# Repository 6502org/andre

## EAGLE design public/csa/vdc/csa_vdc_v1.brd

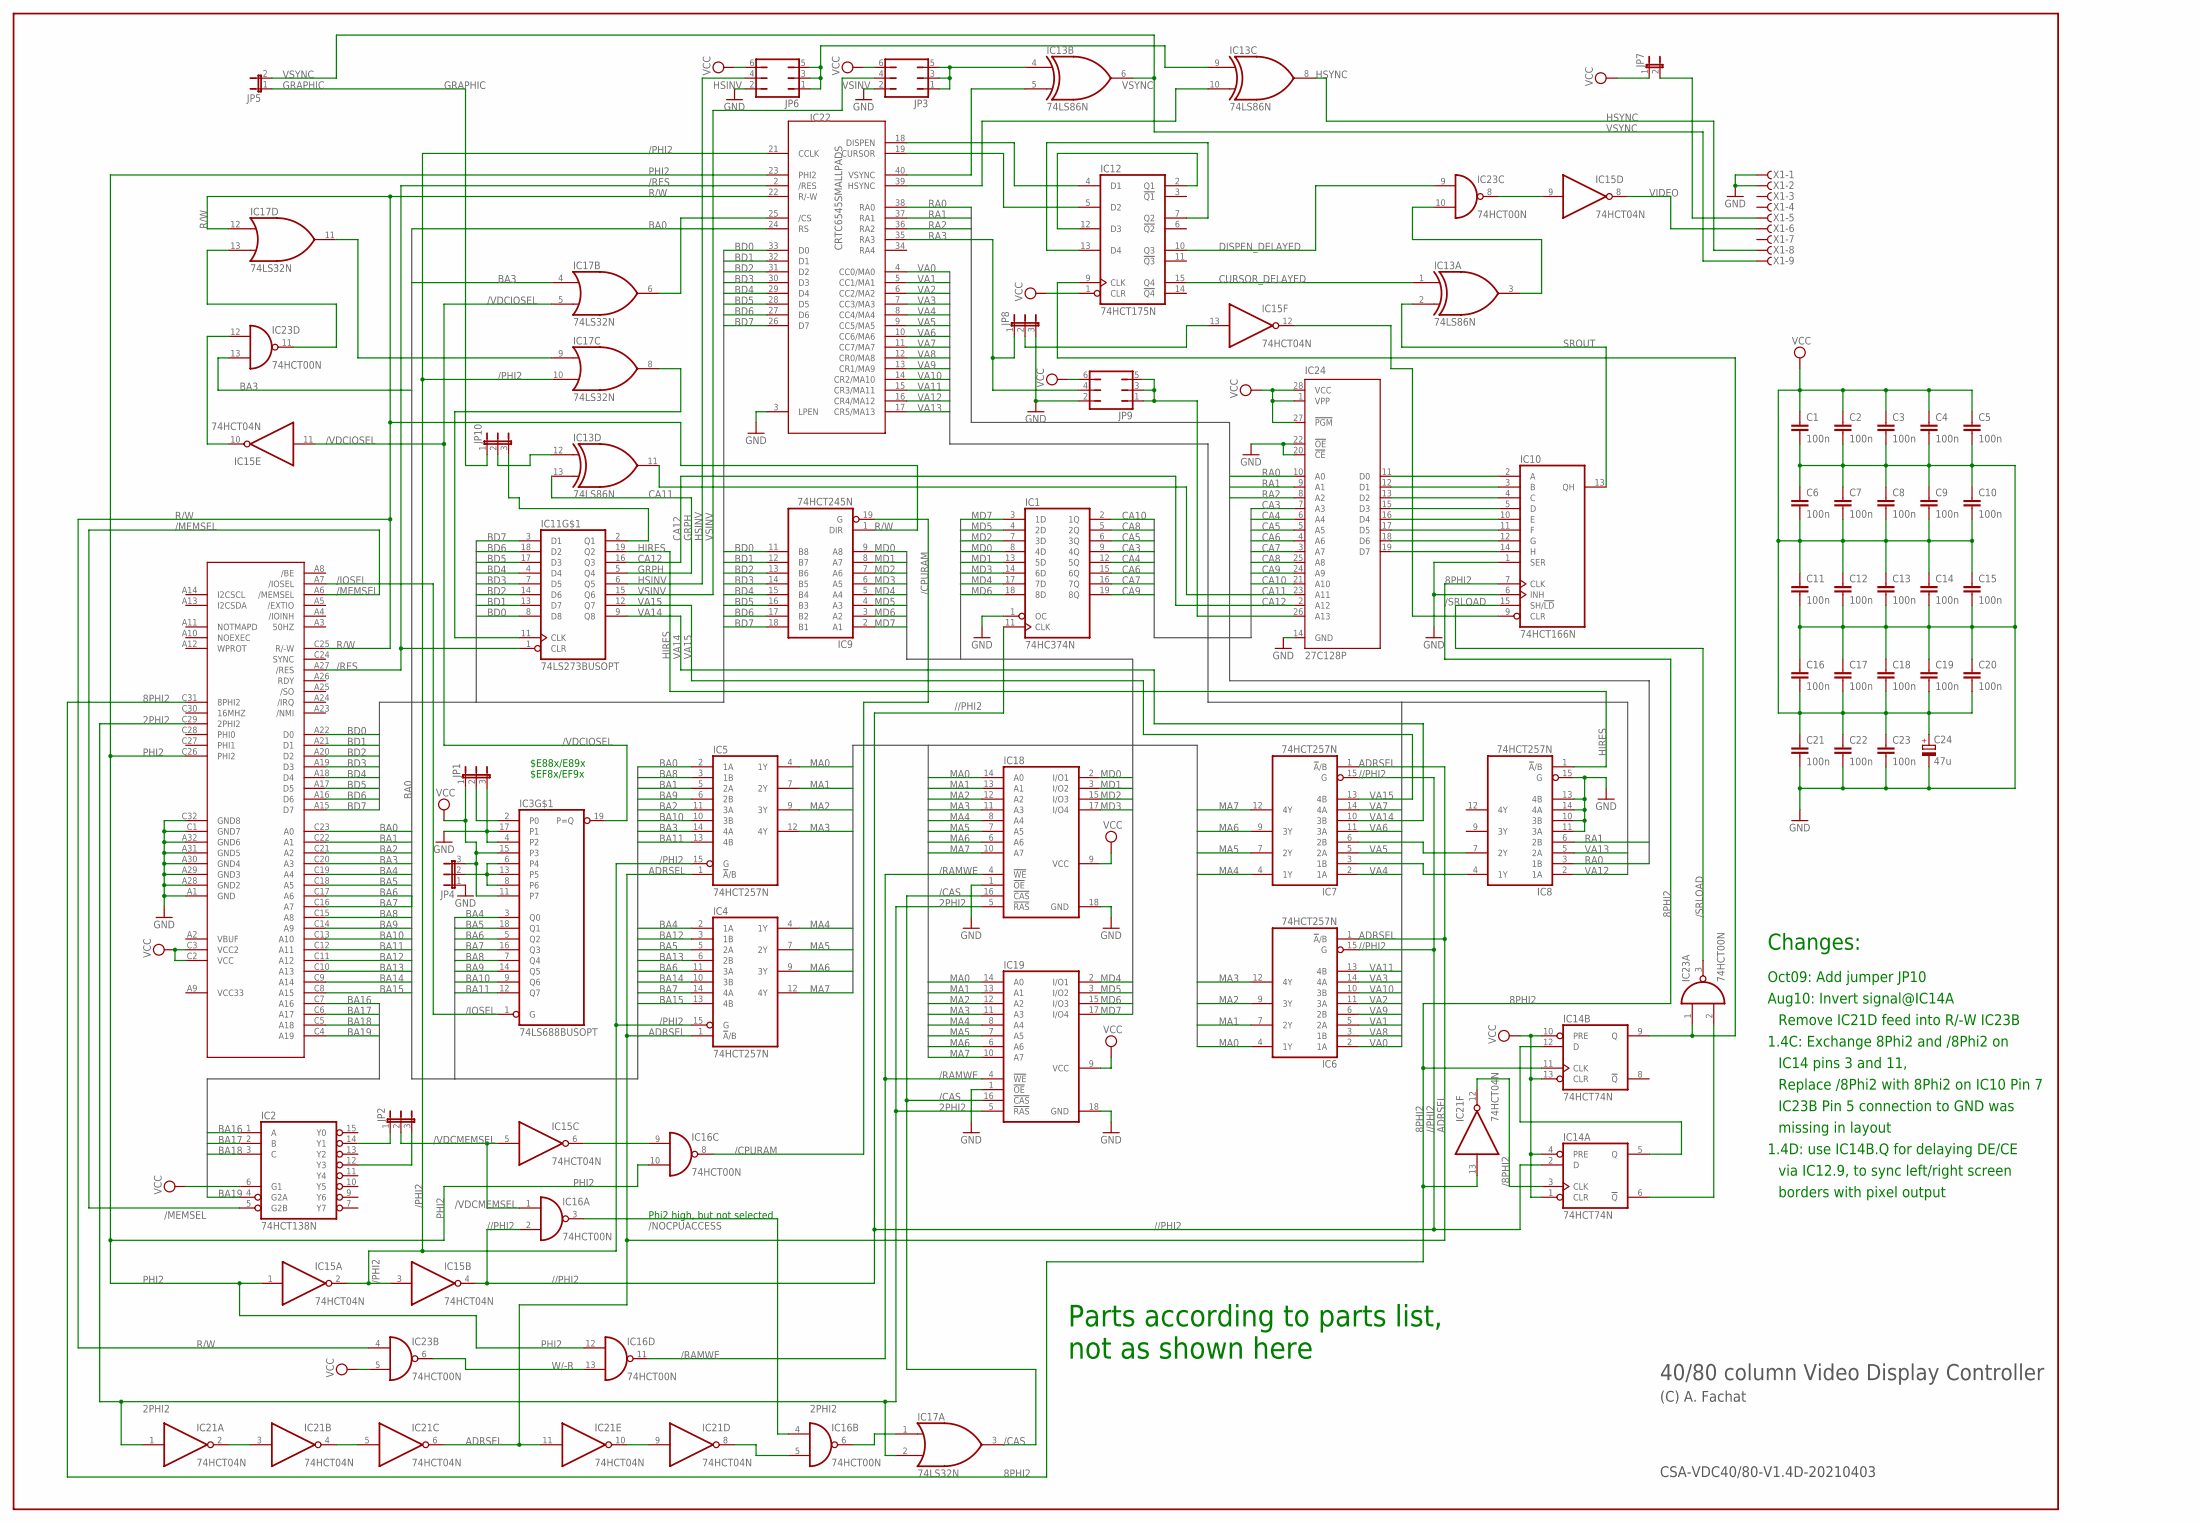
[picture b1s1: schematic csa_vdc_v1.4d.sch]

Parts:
C1, C2, C3, C4, C5, C6, C7, C8, C9, C10, C11, C12, C13, C14, C15, C16, C17, C18, C19, C20, C21, C22, C23: 100n; C025-025X050
C24: 47u; E2,5-5
IC1: 74HC374N; DIL20
IC2: 74HCT138N; DIL16
IC3: 74LS688BUSOPT; DIL20
IC4, IC5, IC6, IC7, IC8: 74HCT257N; DIL16
IC9: 74HCT245N; DIL20
IC10: 74HCT166N; DIL16
IC11: 74LS273BUSOPT; DIL20
IC12: 74HCT175N; DIL16
IC13: 74LS86N; DIL14
IC14: 74HCT74N; DIL14
IC15, IC21: 74HCT04N; DIL14
IC16, IC23: 74HCT00N; DIL14
IC17: 74LS32N; DIL14
IC18, IC19: 41464C; DIL18
IC22: CRTC6545SMALLPADS; DIP40
IC24: 27C128P; DIL28-6
JP1, JP2, JP4, JP8, JP10: JP2E; JP2
JP3, JP6, JP9: JP3Q
JP5, JP7: JP1E; JP1
U$1: CSABUS
X1: F09HPS; F09HP

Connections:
2PHI2: IC17.2 (I1), IC18.5 (!RAS), IC19.5 (!RAS), IC21.1 (I), U$1.C29 (2PHI2)
8PHI2: IC10.7 (CLK), IC14.11 (CLK), IC21.13 (I), U$1.C31 (8PHI2)
/8PHI2: IC14.3 (CLK), IC21.12 (O)
//PHI2: IC1.11 (CLK), IC6.15 (G), IC7.15 (G), IC14.2 (D), IC15.4 (O), IC16.2 (I1)
/CAS: IC17.3 (O), IC18.16 (!CAS), IC19.16 (!CAS)
/CPURAM: IC9.19 (G), IC16.8 (O)
/IOSEL: IC3.1 (G), U$1.A7 (/IOSEL)
/MEMSEL: IC2.5 (G2B), U$1.A6 (/MEMSEL)
/NOCPUACCESS: IC16.3 (O), IC16.4 (I0)
/PHI2: IC4.15 (G), IC5.15 (G), IC15.2 (O), IC15.3 (I), IC17.10 (I1), IC22.21 (CCLK)
/RAMWE: IC16.11 (O), IC18.4 (!WE), IC19.4 (!WE)
/RES: IC11.1 (CLR), IC22.2 (/RES), U$1.A27 (/RES)
/SRLOAD: IC10.15 (SH/!LD), IC23.3 (O)
/VDCIOSEL: IC3.19 (P=Q), IC15.11 (I), IC17.5 (I1)
/VDCMEMSEL: IC15.5 (I), IC16.1 (I0), JP2.2
ADRSEL: IC4.1 (!A!/B), IC5.1 (!A!/B), IC6.1 (!A!/B), IC7.1 (!A!/B), IC21.6 (O), IC21.11 (I)
BA0: IC5.2 (1A), IC22.24 (RS), U$1.C23 (A0)
BA1: IC5.5 (2A), U$1.C22 (A1)
BA2: IC5.11 (3A), U$1.C21 (A2)
BA3: IC5.14 (4A), IC17.4 (I0), IC23.13 (I1), U$1.C20 (A3)
BA4: IC3.3 (Q0), IC4.2 (1A), U$1.C19 (A4)
BA5: IC3.18 (Q1), IC4.5 (2A), U$1.C18 (A5)
BA6: IC3.5 (Q2), IC4.11 (3A), U$1.C17 (A6)
BA7: IC3.16 (Q3), IC4.14 (4A), U$1.C16 (A7)
BA8: IC3.7 (Q4), IC5.3 (1B), U$1.C15 (A8)
BA9: IC3.14 (Q5), IC5.6 (2B), U$1.C14 (A9)
BA10: IC3.9 (Q6), IC5.10 (3B), U$1.C13 (A10)
BA11: IC3.12 (Q7), IC5.13 (4B), U$1.C12 (A11)
BA12: IC4.3 (1B), U$1.C11 (A12)
BA13: IC4.6 (2B), U$1.C10 (A13)
BA14: IC4.10 (3B), U$1.C9 (A14)
BA15: IC4.13 (4B), U$1.C8 (A15)
BA16: IC2.1 (A), U$1.C7 (A16)
BA17: IC2.2 (B), U$1.C6 (A17)
BA18: IC2.3 (C), U$1.C5 (A18)
BA19: IC2.4 (G2A), U$1.C4 (A19)
BD0: IC9.11 (B8), IC11.8 (D8), IC22.33 (D0), U$1.A22 (D0)
BD1: IC9.12 (B7), IC11.13 (D7), IC22.32 (D1), U$1.A21 (D1)
BD2: IC9.13 (B6), IC11.14 (D6), IC22.31 (D2), U$1.A20 (D2)
BD3: IC9.14 (B5), IC11.7 (D5), IC22.30 (D3), U$1.A19 (D3)
BD4: IC9.15 (B4), IC11.4 (D4), IC22.29 (D4), U$1.A18 (D4)
BD5: IC9.16 (B3), IC11.17 (D3), IC22.28 (D5), U$1.A17 (D5)
BD6: IC9.17 (B2), IC11.18 (D2), IC22.27 (D6), U$1.A16 (D6)
BD7: IC9.18 (B1), IC11.3 (D1), IC22.26 (D7), U$1.A15 (D7)
CA3: IC1.9 (4Q), IC24.7 (A3)
CA4: IC1.12 (5Q), IC24.6 (A4)
CA5: IC1.6 (3Q), IC24.5 (A5)
CA6: IC1.15 (6Q), IC24.4 (A6)
CA7: IC1.16 (7Q), IC24.3 (A7)
CA8: IC1.5 (2Q), IC24.25 (A8)
CA9: IC1.19 (8Q), IC24.24 (A9)
CA10: IC1.2 (1Q), IC24.21 (A10)
CA11: IC13.11 (O), IC24.23 (A11)
CA12: IC11.16 (Q3), IC24.2 (A12)
CURSOR_DELAYED: IC12.15 (Q4), IC13.1 (I0)
DISPEN_DELAYED: IC12.10 (Q3), IC23.9 (I0)
GND: C1.2, C2.2, C3.2, C4.2, C5.2, C6.1, C7.1, C8.1, C9.1, C10.1, C11.2, C12.2, C13.2, C14.2, C15.2, C16.1, C17.1, C18.1, C19.1, C20.1, C21.2, C22.2, C23.2, C24.-, IC1.1 (OC), IC1.10 (GND), IC2.8 (GND), IC3.4 (P2), IC3.10 (GND), IC3.17 (P1), IC4.8 (GND), IC5.8 (GND), IC6.8 (GND), IC7.8 (GND), IC8.8 (GND), IC8.10 (3B), IC8.11 (3A), IC8.13 (4B), IC8.14 (4A), IC8.15 (G), IC9.10 (GND), IC10.1 (SER), IC10.6 (INH), IC10.8 (GND), IC11.10 (GND), IC12.8 (GND), IC13.7 (GND), IC14.7 (GND), IC15.7 (GND), IC16.7 (GND), IC17.7 (GND), IC18.1 (!OE), IC18.18 (GND), IC19.1 (!OE), IC19.18 (GND), IC21.7 (GND), IC22.1 (GND), IC22.3 (LPEN), IC23.7 (GND), IC24.14 (GND), IC24.20 (!CE), IC24.22 (!OE), JP1.3, JP3.2, JP4.1, JP6.2, JP8.3, JP9.2, U$1.A1 (GND), U$1.A28 (GND2), U$1.A29 (GND3), U$1.A30 (GND4), U$1.A31 (GND5), U$1.A32 (GND6), U$1.C1 (GND7), U$1.C32 (GND8), X1.1, X1.2
GRAPHIC: JP5.1, JP10.1
GRPH: IC11.5 (Q4), IC13.13 (I1)
HIRES: IC8.1 (!A!/B), IC11.19 (Q2)
HSINV: IC11.6 (Q5), JP6.4
HSYNC: IC13.8 (O), X1.8
MA0: IC5.4 (1Y), IC6.4 (1Y), IC18.14 (A0), IC19.14 (A0)
MA1: IC5.7 (2Y), IC6.7 (2Y), IC18.13 (A1), IC19.13 (A1)
MA2: IC5.9 (3Y), IC6.9 (3Y), IC18.12 (A2), IC19.12 (A2)
MA3: IC5.12 (4Y), IC6.12 (4Y), IC18.11 (A3), IC19.11 (A3)
MA4: IC4.4 (1Y), IC7.4 (1Y), IC18.8 (A4), IC19.8 (A4)
MA5: IC4.7 (2Y), IC7.7 (2Y), IC18.7 (A5), IC19.7 (A5)
MA6: IC4.9 (3Y), IC7.9 (3Y), IC18.6 (A6), IC19.6 (A6)
MA7: IC4.12 (4Y), IC7.12 (4Y), IC18.10 (A7), IC19.10 (A7)
MD0: IC1.8 (4D), IC9.9 (A8), IC18.2 (I/O1)
MD1: IC1.13 (5D), IC9.8 (A7), IC18.3 (I/O2)
MD2: IC1.7 (3D), IC9.7 (A6), IC18.15 (I/O3)
MD3: IC1.14 (6D), IC9.6 (A5), IC18.17 (I/O4)
MD4: IC1.17 (7D), IC9.5 (A4), IC19.2 (I/O1)
MD5: IC1.4 (2D), IC9.4 (A3), IC19.3 (I/O2)
MD6: IC1.18 (8D), IC9.3 (A2), IC19.15 (I/O3)
MD7: IC1.3 (1D), IC9.2 (A1), IC19.17 (I/O4)
unnamed: IC7.3 (1B), IC8.4 (1Y)
unnamed: IC3.2 (P0), JP1.2
unnamed: IC7.6 (2B), IC8.7 (2Y)
unnamed: IC10.2 (A), IC24.11 (D0)
unnamed: IC10.3 (B), IC24.12 (D1)
unnamed: IC10.4 (C), IC24.13 (D2)
unnamed: IC10.5 (D), IC24.15 (D3)
unnamed: IC10.10 (E), IC24.16 (D4)
unnamed: IC10.11 (F), IC24.17 (D5)
unnamed: IC10.12 (G), IC24.18 (D6)
unnamed: IC10.14 (H), IC24.19 (D7)
unnamed: IC2.14 (Y1), JP2.1
unnamed: IC2.12 (Y3), JP2.3
unnamed: IC14.6 (!Q), IC23.2 (I1)
unnamed: IC12.9 (CLK), IC14.9 (Q), IC23.1 (I0)
unnamed: IC11.11 (CLK), IC17.8 (O)
unnamed: IC12.4 (D1), IC22.18 (DISPEN)
unnamed: IC3.6 (P4), IC3.8 (P6), IC3.13 (P5), JP4.2
unnamed: IC21.2 (O), IC21.3 (I)
unnamed: IC21.4 (O), IC21.5 (I)
unnamed: IC12.5 (D2), IC22.19 (CURSOR)
unnamed: IC21.9 (I), IC21.10 (O)
unnamed: IC13.9 (I0), JP6.1, JP6.3, JP6.5
unnamed: IC16.5 (I1), IC21.8 (O)
unnamed: IC16.6 (O), IC17.1 (I0)
unnamed: IC17.13 (I1), IC23.11 (O)
unnamed: IC15.6 (O), IC16.9 (I0)
unnamed: IC12.2 (Q1), IC12.12 (D3)
unnamed: IC12.7 (Q2), IC12.13 (D4)
unnamed: IC13.4 (I0), JP3.1, JP3.3, JP3.5
unnamed: IC10.9 (CLR), IC15.12 (O)
unnamed: IC13.3 (O), IC23.10 (I1)
unnamed: JP7.2, X1.5
unnamed: IC15.9 (I), IC23.8 (O)
unnamed: IC14.5 (Q), IC14.12 (D)
unnamed: IC13.5 (I1), IC22.40 (VSYNC)
unnamed: IC15.13 (I), JP8.2
unnamed: IC24.26 (A13), JP9.1, JP9.3, JP9.5
unnamed: IC13.10 (I1), IC22.39 (HSYNC)
unnamed: IC11.2 (Q1), JP10.3
unnamed: IC13.12 (I0), JP10.2
unnamed: IC17.6 (O), IC22.25 (/CS)
unnamed: IC15.10 (O), IC23.12 (I0)
unnamed: IC17.9 (I0), IC17.11 (O)
PHI2: IC15.1 (I), IC16.10 (I1), IC16.12 (I0), IC22.23 (PHI2), U$1.C26 (PHI2)
R/W: IC9.1 (DIR), IC17.12 (I0), IC22.22 (R/-W), IC23.4 (I0), U$1.C25 (R/-W)
RA0: IC8.3 (1B), IC22.38 (RA0), IC24.10 (A0)
RA1: IC8.6 (2B), IC22.37 (RA1), IC24.9 (A1)
RA2: IC22.36 (RA2), IC24.8 (A2)
RA3: IC22.35 (RA3), JP8.1, JP9.4
SROUT: IC10.13 (QH), IC13.2 (I1)
VA0: IC6.2 (1A), IC22.4 (CC0/MA0)
VA1: IC6.5 (2A), IC22.5 (CC1/MA1)
VA2: IC6.11 (3A), IC22.6 (CC2/MA2)
VA3: IC6.14 (4A), IC22.7 (CC3/MA3)
VA4: IC7.2 (1A), IC22.8 (CC4/MA4)
VA5: IC7.5 (2A), IC22.9 (CC5/MA5)
VA6: IC7.11 (3A), IC22.10 (CC6/MA6)
VA7: IC7.14 (4A), IC22.11 (CC7/MA7)
VA8: IC6.3 (1B), IC22.12 (CR0/MA8)
VA9: IC6.6 (2B), IC22.13 (CR1/MA9)
VA10: IC6.10 (3B), IC22.14 (CR2/MA10)
VA11: IC6.13 (4B), IC22.15 (CR3/MA11)
VA12: IC8.2 (1A), IC22.16 (CR4/MA12)
VA13: IC8.5 (2A), IC22.17 (CR5/MA13)
VA14: IC7.10 (3B), IC11.9 (Q8)
VA15: IC7.13 (4B), IC11.12 (Q7)
VCC: C1.1, C2.1, C3.1, C4.1, C5.1, C6.2, C7.2, C8.2, C9.2, C10.2, C11.1, C12.1, C13.1, C14.1, C15.1, C16.2, C17.2, C18.2, C19.2, C20.2, C21.1, C22.1, C23.1, C24.+, IC1.20 (VCC), IC2.6 (G1), IC2.16 (VCC), IC3.11 (P7), IC3.15 (P3), IC3.20 (VCC), IC4.16 (VCC), IC5.16 (VCC), IC6.16 (VCC), IC7.16 (VCC), IC8.16 (VCC), IC9.20 (VCC), IC10.16 (VCC), IC11.20 (VCC), IC12.1 (CLR), IC12.16 (VCC), IC13.14 (VCC), IC14.1 (CLR), IC14.4 (PRE), IC14.10 (PRE), IC14.13 (CLR), IC14.14 (VCC), IC15.14 (VCC), IC16.14 (VCC), IC17.14 (VCC), IC18.9 (VCC), IC19.9 (VCC), IC21.14 (VCC), IC22.20 (VCC), IC23.5 (I1), IC23.14 (VCC), IC24.1 (VPP), IC24.27 (!PGM), IC24.28 (VCC), JP1.1, JP3.6, JP4.3, JP6.6, JP7.1, JP9.6, U$1.C2 (VCC), U$1.C3 (VCC2)
VIDEO: IC15.8 (O), X1.6
VSINV: IC11.15 (Q6), JP3.4
VSYNC: IC13.6 (O), JP5.2, X1.9
W/-R: IC16.13 (I1), IC23.6 (O)

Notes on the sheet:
40/80 column Video Display Controller
CSA-VDC40/80-V1.4D-20210403
(C) A. Fachat
Phi2 high, but not selected
$E88x/E89x
$EF8x/EF9x
Parts according to parts list,
not as shown here
Changes:
Oct09: Add jumper JP10
Aug10: Invert signal@IC14A
Remove IC21D feed into R/-W IC23B
1.4C: Exchange 8Phi2 and /8Phi2 on
Replace /8Phi2 with 8Phi2 on IC10 Pin 7
IC14 pins 3 and 11,
IC23B Pin 5 connection to GND was
missing in layout
1.4D: use IC14B.Q for delaying DE/CE
via IC12.9, to sync left/right screen
borders with pixel output

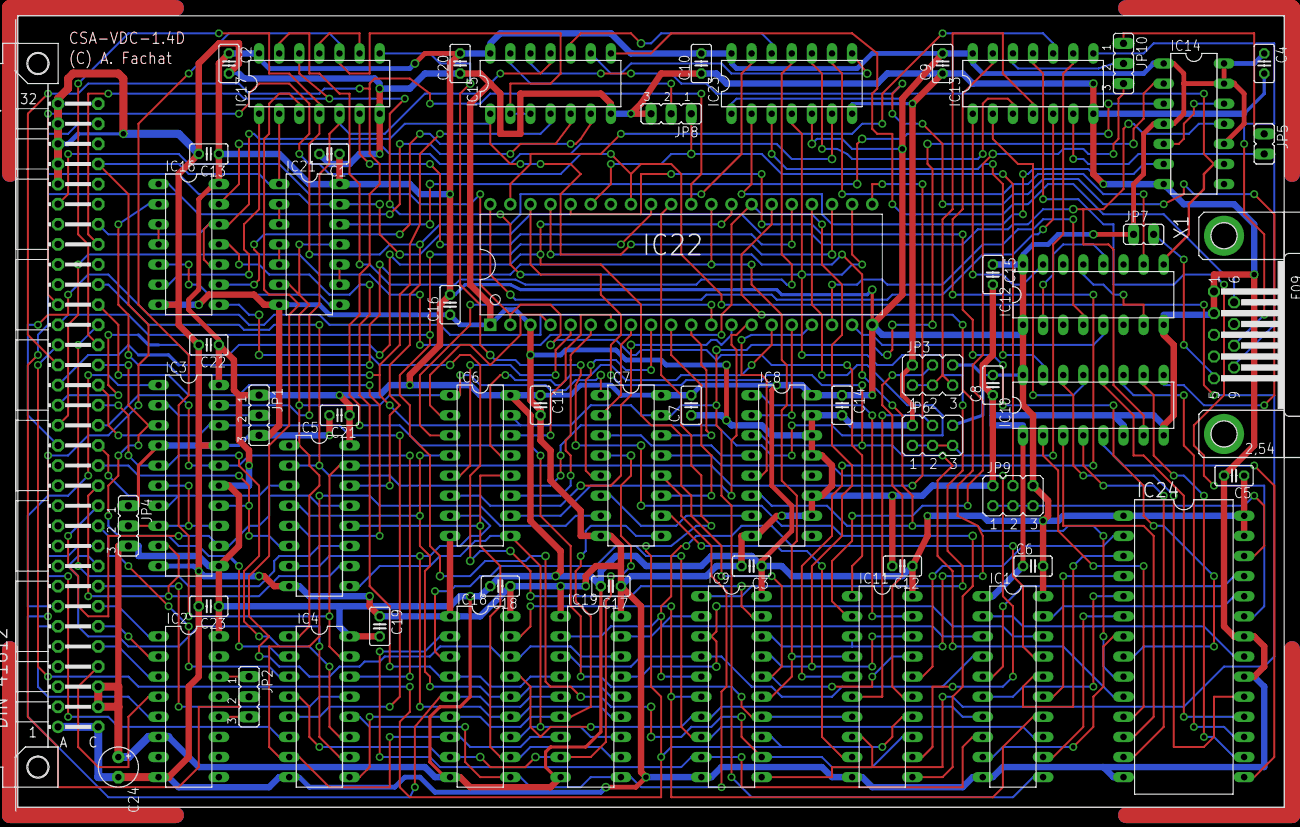
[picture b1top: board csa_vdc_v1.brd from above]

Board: 2 copper layers, 160.0 x 100.0 mm, 59 parts (0 on the bottom side), 150 nets.
